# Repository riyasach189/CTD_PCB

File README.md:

# Collaborators
[@riyasach189](https://github.com/riyasach189)

[@kio42069](https://github.com/kio42069)

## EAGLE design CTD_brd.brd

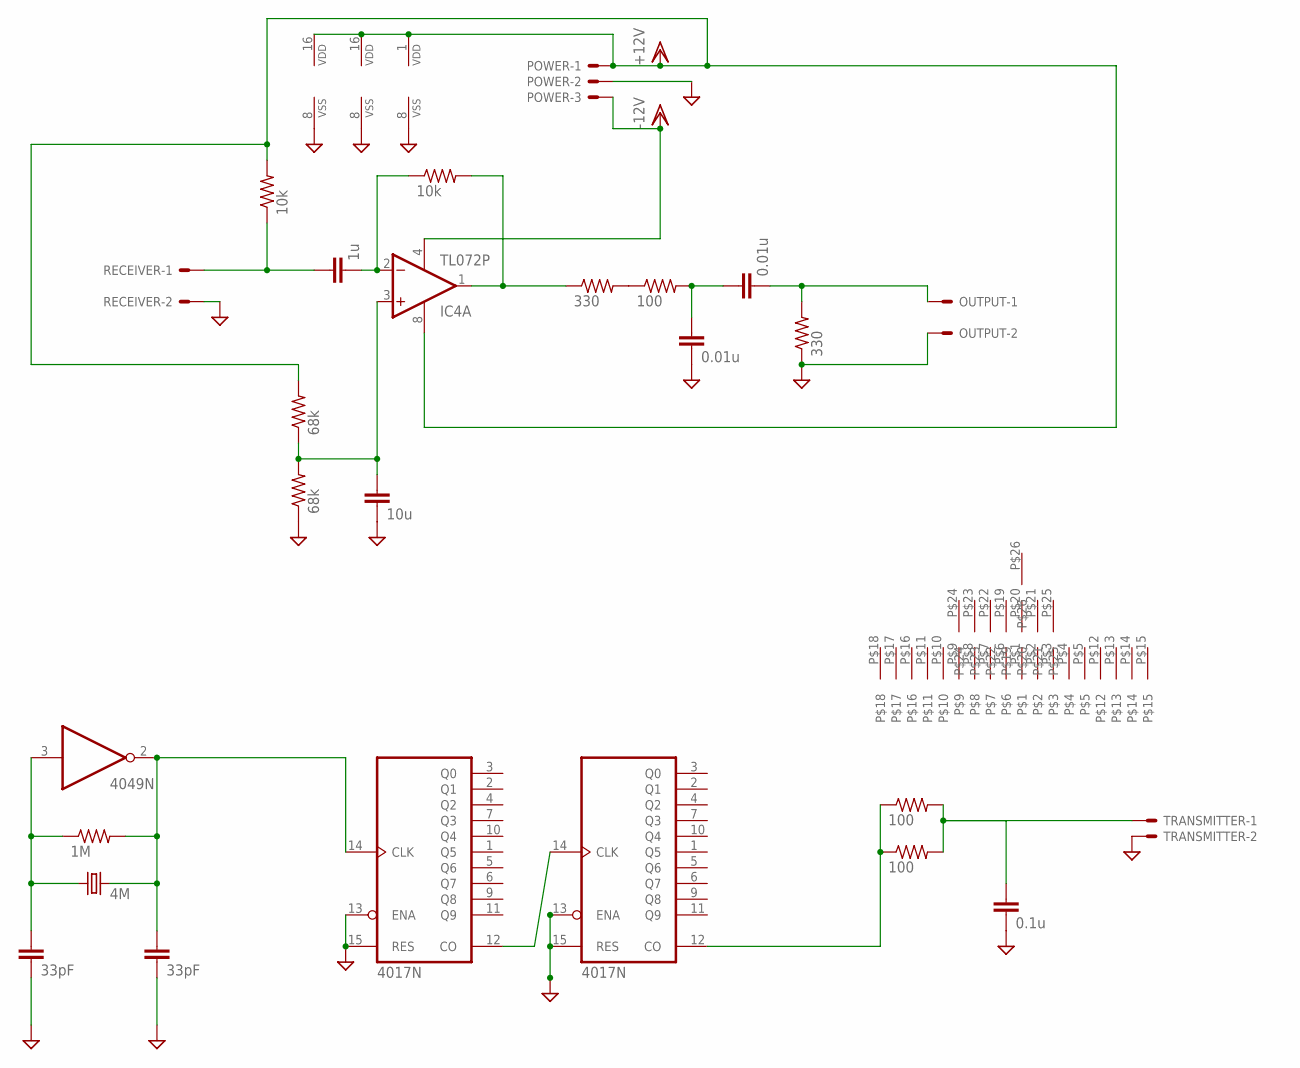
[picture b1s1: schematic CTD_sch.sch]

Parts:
C1, C2: 33pF; C5B3.5
C3: 0.1u; C5B3.5
C4: 10u; C5B3.5
C5: 1u; C5B3.5
C6, C7: 0.01u; C5B3.5
IC1, IC2: 4017N; DIL16
IC3: 4049N; DIL16
IC4: TL072P; DIL08
OUTPUT: C-GRID-02-70543; 70543-02
POWER: C-GRID-03-70543; 70543-03
Q1: 4M; HC49U-V
R1: 1M; 0207/12
R2, R3, R9: 100; 0207/12
R4, R7: 68k; 0207/12
R5, R6: 10k; 0207/12
R8, R10: 330; 0207/12
RECEIVER: C-GRID-02-70543; 70543-02
TRANSMITTER: C-GRID-02-70543; 70543-02
U$1: G-11G-11; G-11

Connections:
GND: C1.2, C2.2, C3.2, C4.2, C6.2, IC1.8 (VSS), IC1.13 (ENA), IC1.15 (RES), IC2.8 (VSS), IC2.13 (ENA), IC2.15 (RES), IC3.8 (VSS), OUTPUT.2, POWER.2, R4.1, R10.1, RECEIVER.2, TRANSMITTER.2
unnamed: C2.1, IC3.3 (I), Q1.1, R1.1
unnamed: C1.1, IC1.14 (CLK), IC3.2 (O), Q1.2, R1.2
unnamed: IC1.12 (CO), IC2.14 (CLK)
unnamed: IC2.12 (CO), R2.1, R3.1
unnamed: C3.1, R2.2, R3.2, TRANSMITTER.1
unnamed: R8.2, R9.1
unnamed: C4.1, IC4.3 (+IN), R4.2, R7.1
unnamed: C5.2, IC4.2 (-IN), R6.1
unnamed: C5.1, R5.1, RECEIVER.1
unnamed: IC4.1 (OUT), R6.2, R8.1
unnamed: C6.1, C7.1, R9.2
unnamed: C7.2, OUTPUT.1, R10.2
unnamed: IC4.4 (V-), POWER.3
VDD: IC1.16 (VDD), IC2.16 (VDD), IC3.1 (VDD), IC4.8 (V+), POWER.1, R5.2, R7.2

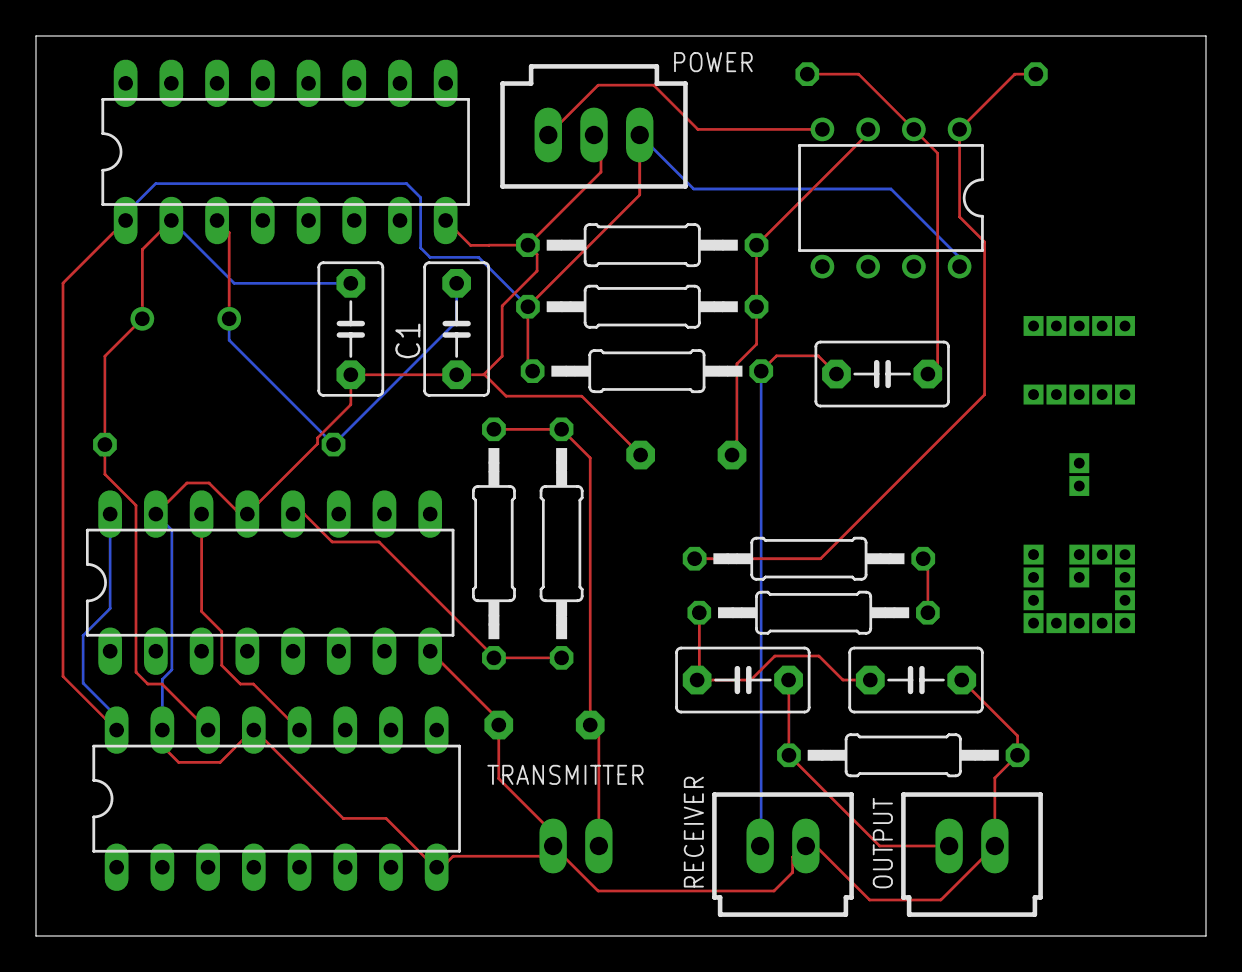
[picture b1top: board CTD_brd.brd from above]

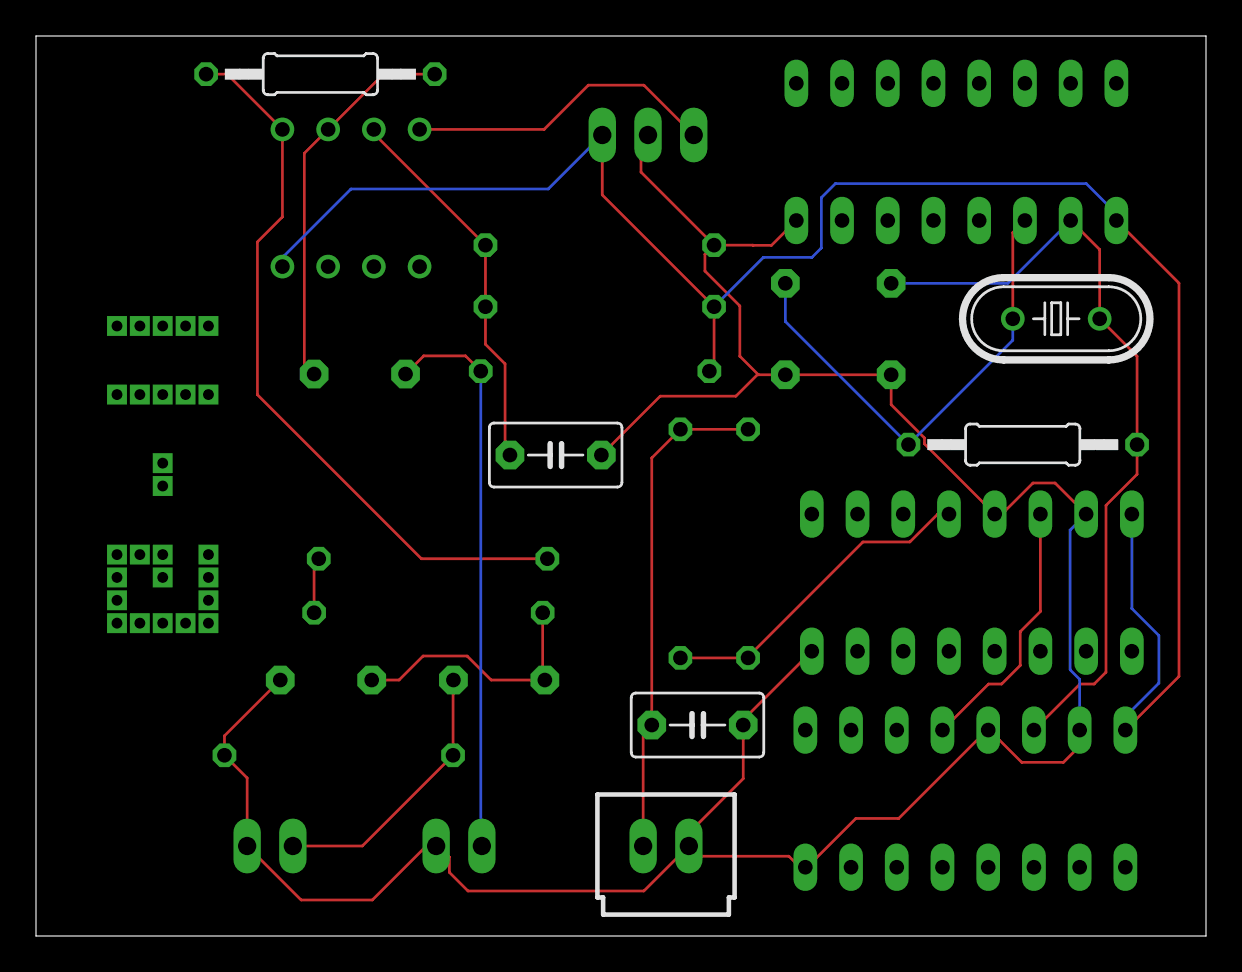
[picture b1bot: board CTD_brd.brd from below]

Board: 2 copper layers, 65.0 x 50.0 mm, 27 parts (6 on the bottom side), 15 nets.

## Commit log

2024-06-30 Rename [Monsoon 2023]CTD Lab 1.pdf to Problem_Statement.pdf
